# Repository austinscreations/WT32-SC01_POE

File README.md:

# WT32-SC01_POE

2023-06-28:

New sheild has been designed that is more universal. the deisgn is much smaller. uses a single 1.25mm jst conenctor to connect to the wt32-sc01 PLUS display.
adapter has been built for the WT32-S3-86s (replaces the 86v) 4" display. adapter in the works to support the orginal display as well

2022-06-23: renamed the repo as this project has evolved

There are now two shields designed for the wt32-sc01 display.
- one offers Ethernet + 802.1af POE
- second offers passive 12-24v POE + a 2.1mm jack

the thought with a passive board is that it's smaller allowing for more compact case designs to be built. and if you prefer to use 802.1af POE with the 2.1mm jack you can very eaily use a standard POE injector that normally cost about $6 from aliexpress to gain such functionality. with teh apssive baord however you are limited to using wifi.

both shields also equipped with qwiic connector for easy i2c support

designed for the use case of using the panel for homeautomation, code and gui in progress.

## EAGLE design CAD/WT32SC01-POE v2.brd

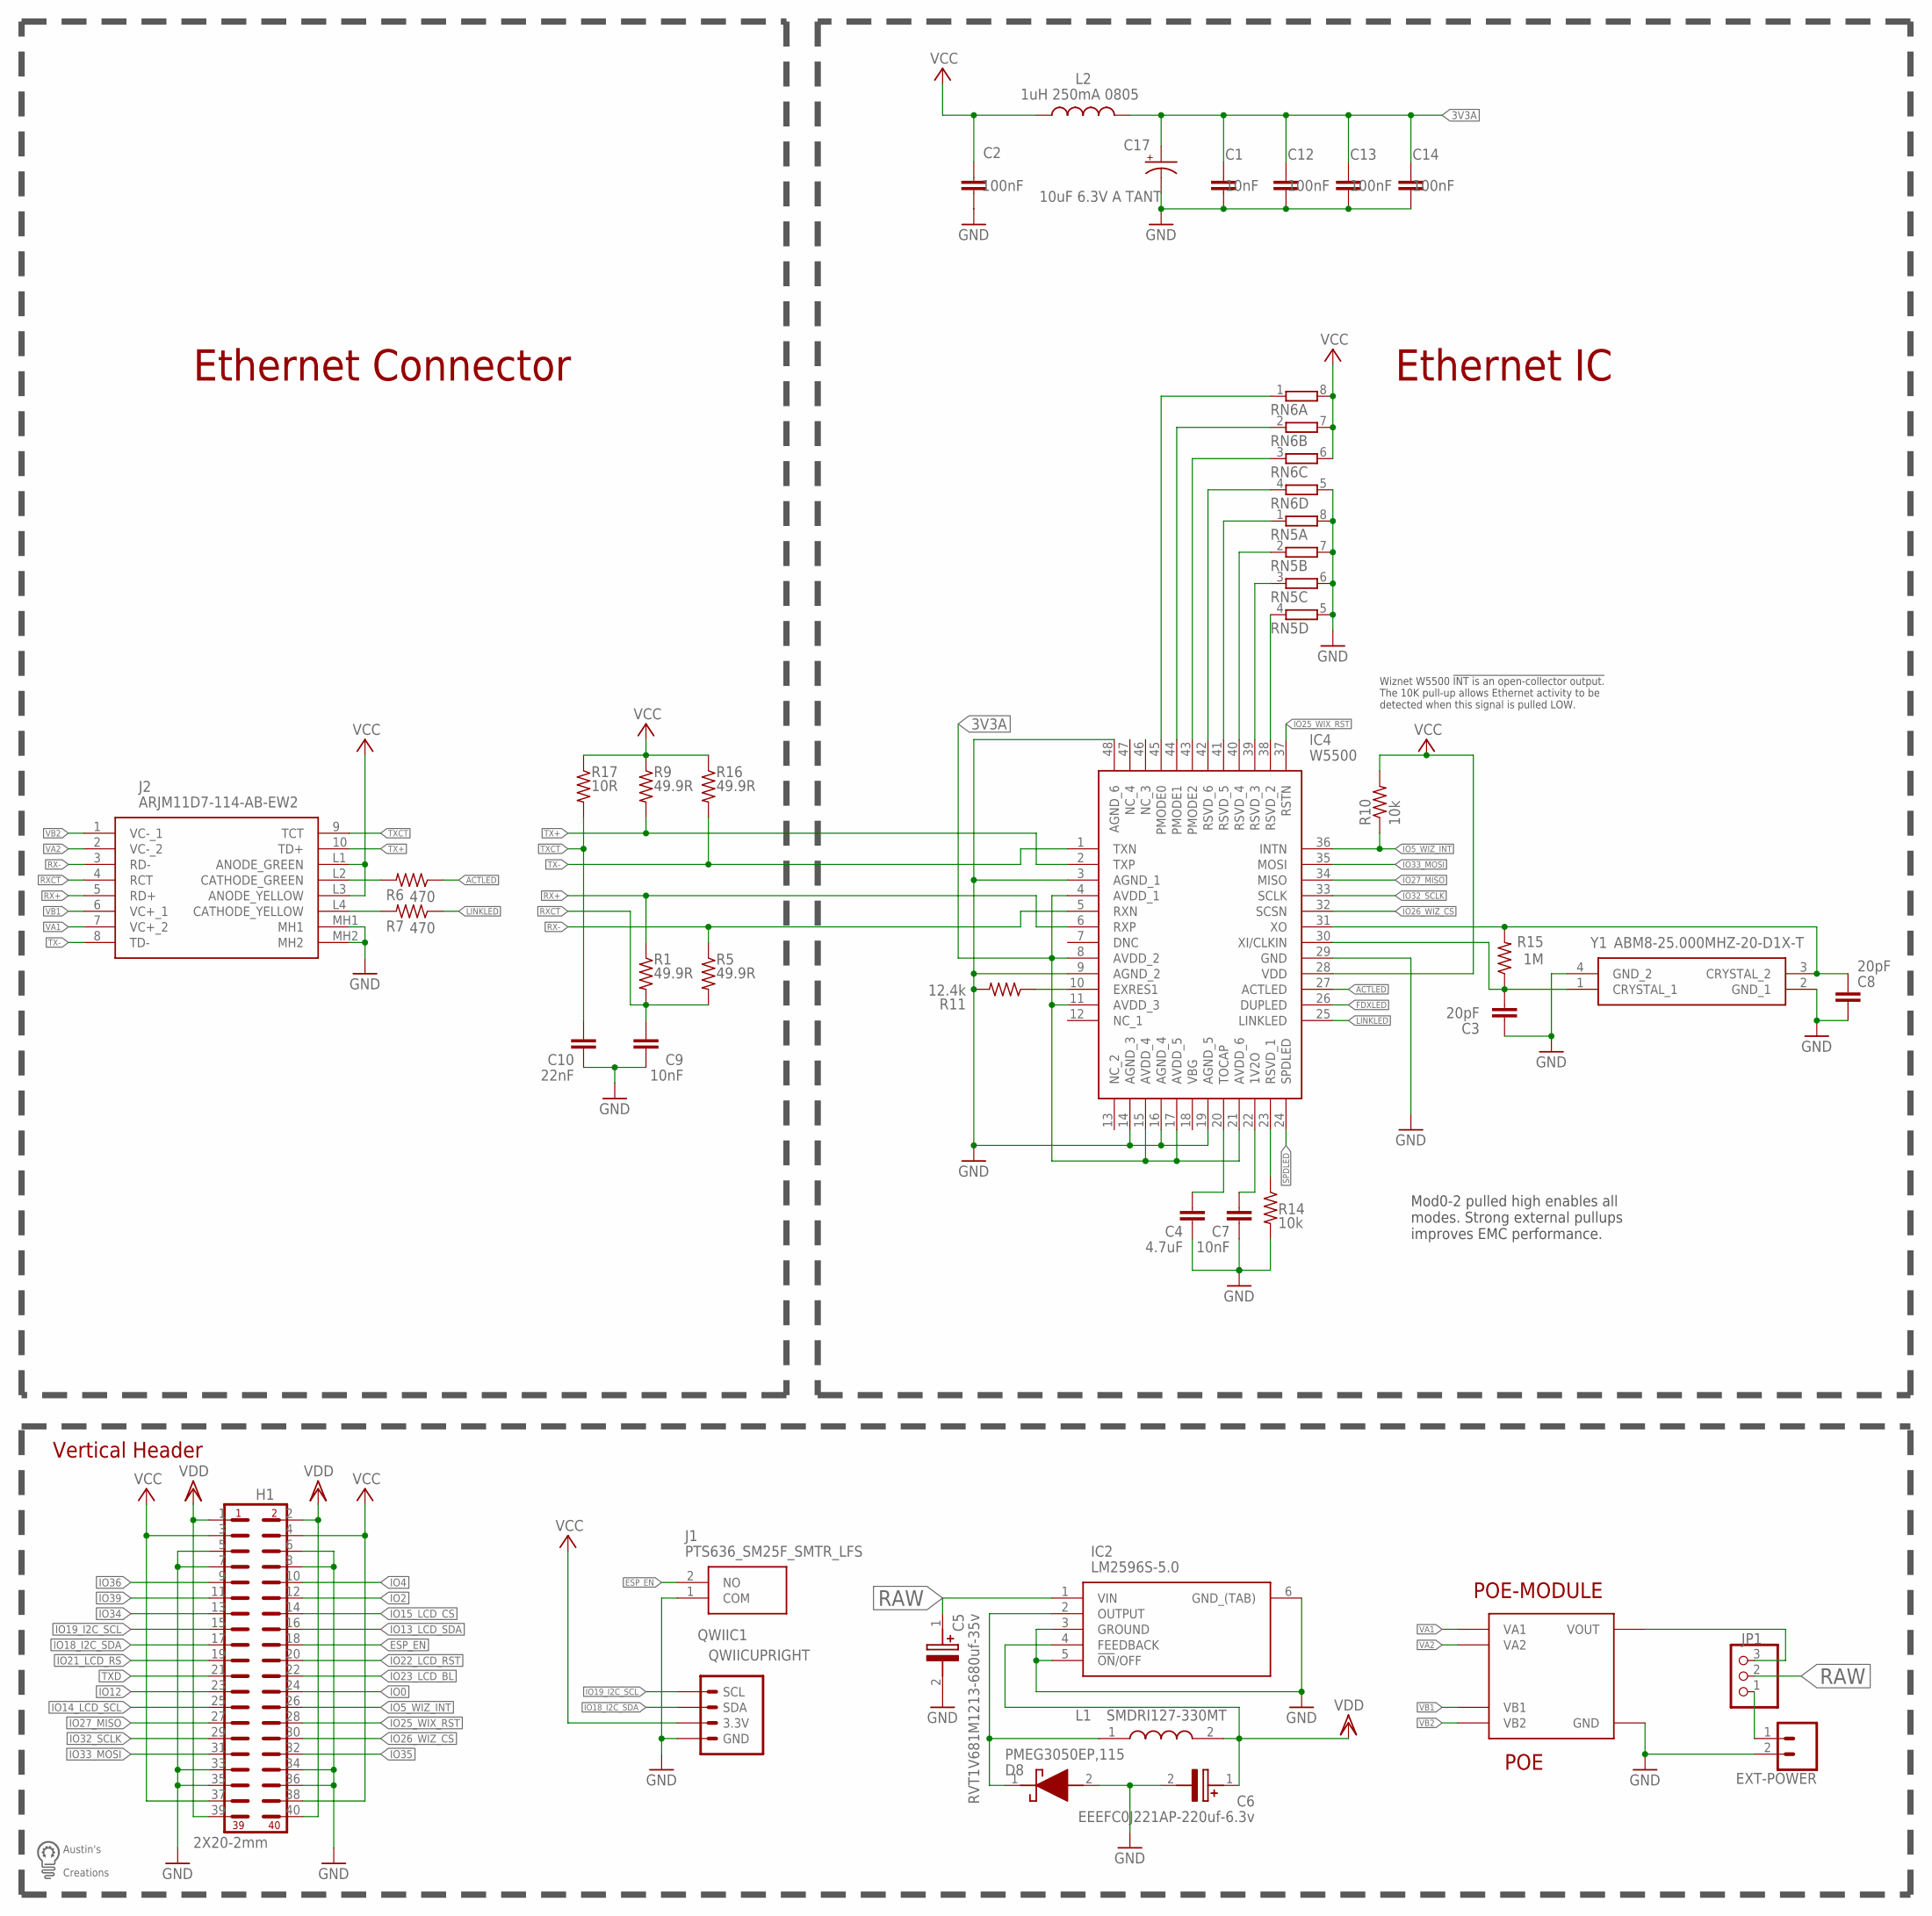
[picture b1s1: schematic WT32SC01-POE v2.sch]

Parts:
C1, C7, C9: 10nF; C0603
C2, C12, C13, C14: 100nF; C0603
C3, C8: 20pF; C0603
C4: 4.7uF; C0603
C5: RVT1V681M1213-680uf-35v; CAPAE1350X1400N
C6: EEEFC0J221AP-220uf-6.3v; CAPAE830X650N
C10: 22nF; C0603
C17: 10uF 6.3V A TANT; A/3216-18W
D8: PMEG3050EP,115; PMEG3050EP115
EXT-POWER: JL301-50002U02; SCREWTERMINAL-5MM-2
H1: 2X20-2mm; 2X20-2.00-P-BELOW
IC2: LM2596S-5.0; TO170P1435X465-6N
IC4: W5500; QFP50P900X900X160-48N
J1: PTS636_SM25F_SMTR_LFS; PTS636SM25FSMTRLFS
J2: ARJM11D7-114-AB-EW2; ARJM11D7114ABEW2
JP1: PINHD-1X3; 1X03
L1: SMDRI127-330MT; INDPM120120X800N
L2: 1uH 250mA 0805; L2012C
POE-MODULE: POE; DP1435
QWIIC1: QWIICUPRIGHT; BM04B-SRSS-TB
R1, R5, R9, R16: 49.9R; R0603
R6, R7: 470; R0603
R10, R14: 10k; R0603
R11: 12.4k; R0603
R15: 1M; R0603
R17: 10R; R0603
RN5, RN6: 4R-N0603-ARC; 0603-ARC
U$1: LOGOMED
Y1: ABM8-25.000MHZ-20-D1X-T; ABM825000MHZ10B1UT

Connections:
3V3A: C1.1, C12.1, C13.1, C14.1, C17.+, IC4.4 (AVDD_1), IC4.8 (AVDD_2), IC4.11 (AVDD_3), IC4.15 (AVDD_4), IC4.17 (AVDD_5), IC4.21 (AVDD_6), L2.2
ACTLED: IC4.27 (ACTLED), R6.1
ESP_EN: H1.18, J1.2 (NO)
FDXLED: IC4.26 (DUPLED)
GND: C1.2, C2.2, C3.1, C4.1, C5.2 (-), C6.2 (-), C7.1, C8.1, C9.1, C10.1, C12.2, C13.2, C14.2, C17.-, D8.2 (A), EXT-POWER.2, H1.5, H1.6, H1.7, H1.8, H1.33, H1.34, H1.35, H1.36, IC2.3 (GROUND), IC2.5 (!ON!/OFF), IC2.6 (GND_(TAB)), IC4.3 (AGND_1), IC4.9 (AGND_2), IC4.14 (AGND_3), IC4.16 (AGND_4), IC4.19 (AGND_5), IC4.29 (GND), IC4.48 (AGND_6), J1.1 (COM), J2.MH1, J2.MH2, POE-MODULE.GND, QWIIC1.1 (GND), R11.2, R14.2, RN5.5 (2), RN5.6 (2), RN5.7 (2), RN5.8 (2), RN6.5 (2), Y1.2 (GND_1), Y1.4 (GND_2)
IO0: H1.24
IO2: H1.12
IO4: H1.10
IO5_WIZ_INT: H1.26, IC4.36 (INTN), R10.1
IO12: H1.23
IO13_LCD_SDA: H1.16
IO14_LCD_SCL: H1.25
IO15_LCD_CS: H1.14
IO18_I2C_SDA: H1.17, QWIIC1.3 (SDA)
IO19_I2C_SCL: H1.15, QWIIC1.4 (SCL)
IO21_LCD_RS: H1.19
IO22_LCD_RST: H1.20
IO23_LCD_BL: H1.22
IO25_WIX_RST: H1.28, IC4.37 (RSTN)
IO26_WIZ_CS: H1.30, IC4.32 (SCSN)
IO27_MISO: H1.27, IC4.34 (MISO)
IO32_SCLK: H1.29, IC4.33 (SCLK)
IO33_MOSI: H1.31, IC4.35 (MOSI)
IO34: H1.13
IO35: H1.32
IO36: H1.9
IO39: H1.11
LINKLED: IC4.25 (LINKLED), R7.1
unnamed: EXT-POWER.1, JP1.1
unnamed: IC4.10 (EXRES1), R11.1
unnamed: IC4.23 (RSVD_1), R14.1
unnamed: IC4.38 (RSVD_2), RN5.4 (1)
unnamed: IC4.39 (RSVD_3), RN5.3 (1)
unnamed: IC4.40 (RSVD_4), RN5.2 (1)
unnamed: IC4.41 (RSVD_5), RN5.1
unnamed: IC4.42 (RSVD_6), RN6.4 (1)
unnamed: C8.2, IC4.31 (XO), R15.2, Y1.3 (CRYSTAL_2)
unnamed: IC4.43 (PMODE2), RN6.3 (1)
unnamed: IC4.44 (PMODE1), RN6.2 (1)
unnamed: IC4.45 (PMODE0), RN6.1
unnamed: C3.2, IC4.30 (XI/CLKIN), R15.1, Y1.1 (CRYSTAL_1)
unnamed: JP1.3, POE-MODULE.VOUT
unnamed: J2.L2 (CATHODE_GREEN), R6.2
unnamed: D8.1 (K), IC2.2 (OUTPUT), L1.1
unnamed: J2.L4 (CATHODE_YELLOW), R7.2
unnamed: C7.2, IC4.22 (1V2O)
unnamed: C4.2, IC4.20 (TOCAP)
RAW: C5.1 (+), IC2.1 (VIN), JP1.2
RX+: IC4.6 (RXP), J2.5 (RD+), R1.1
RX-: IC4.5 (RXN), J2.3 (RD-), R5.1
RXCT: C9.2, J2.4 (RCT), R1.2, R5.2
SPDLED: IC4.24 (SPDLED)
TX+: IC4.2 (TXP), J2.10 (TD+), R9.2
TX-: IC4.1 (TXN), J2.8 (TD-), R16.2
TXCT: C10.2, J2.9 (TCT), R17.2
TXD: H1.21
VA1: J2.7 (VC+_2), POE-MODULE.VA1
VA2: J2.2 (VC-_2), POE-MODULE.VA2
VB1: J2.6 (VC+_1), POE-MODULE.VB1
VB2: J2.1 (VC-_1), POE-MODULE.VB2
VCC: C2.1, H1.3, H1.4, H1.37, H1.38, IC4.28 (VDD), J2.L1 (ANODE_GREEN), J2.L3 (ANODE_YELLOW), L2.1, QWIIC1.2 (3.3V), R9.1, R10.2, R16.1, R17.1, RN6.6 (2), RN6.7 (2), RN6.8 (2)
VDD: C6.1 (+), H1.1, H1.2, H1.39, H1.40, IC2.4 (FEEDBACK), L1.2

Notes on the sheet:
Vertical Header
Mod0-2 pulled high enables all modes. Strong external pullups improves EMC performance.
Wiznet W5500 !INT is an open-collector output. The 10K pull-up allows Ethernet activity to be detected when this signal is pulled LOW.
Ethernet IC
Ethernet Connector

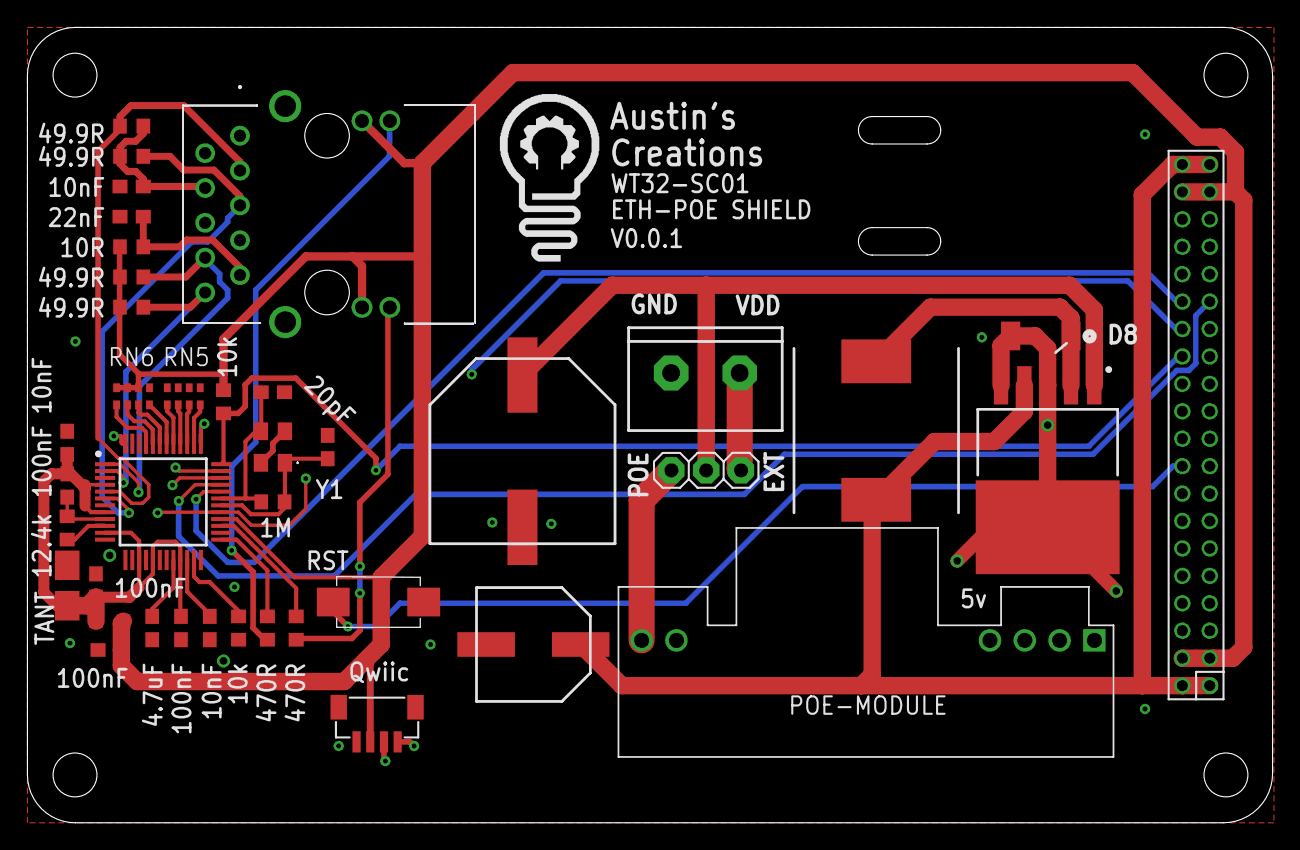
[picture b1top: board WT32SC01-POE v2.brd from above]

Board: 4 copper layers, 90.8 x 58.0 mm, 41 parts (0 on the bottom side), 45 nets.

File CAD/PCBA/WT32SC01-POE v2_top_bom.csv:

Comment,Designator,Footprint,LCSC Part #
1M,R15,R0603,C328343
1uH 250mA 0805,L2,L2012C,C98325
4.7uF,C4,C0603,C152930
10R,R17,R0603,C103222
10k,R10 R14,R0603,C103199
10nF,C1 C7 C9,C0603,C141077
10uF 6.3V A TANT,C17,A/3216-18W,C127946
12.4k,R11,R0603,C269455
20pF,C3 C8,C0603,C105621
22nF,C10,C0603,C302044
49.9R,R1 R5 R9 R16,R0603,C103679 
100nF,C2 C12 C13 C14,C0603,C83060
470R,R6 R7,R0603,C25241 
ABM8-25.000MHZ-20-D1X-T,Y1,ABM825000MHZ10B1UT,C258949
EEEFC0J221AP-220uf-6.3v,C6,CAPAE830X650N,C401613
LM2596S-5.0,IC2,TO170P1435X465-6N,C347421
PMEG4050EP 115,D8,PMEG4050EP115,C96235
PTS636_SM25F_SMTR_LFS,J1,PTS636SM25FSMTRLFS,C410373
QWIICUPRIGHT,QWIIC1,BM04B-SRSS-TB,C145961
RVT1V681M1213-680uf-35v,C5,CAPAE1350X1400N,C98216
SMDRI127-330MT,L1,INDPM120120X800N,C9400 
W5500,IC4,QFP50P900X900X160-48N,C32843
10k,RN5 RN6,R1206,C29718

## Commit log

2022-03-18 adding custom 3d printable wall plate mount
2022-03-18 example code
2022-03-26 accidental upload
2022-06-23 update for new boards
2022-06-23 preparing repo overhaul
2022-06-23 add new wifi and ethernet designs
2022-06-28 new versions
2022-06-28 obsolete design
2022-06-29 add case option for no usb
2022-06-29 add no usb case options
2023-06-28 adding latest POE shield
2023-08-02 adding 86s panel support
2023-08-02 add schematic image
2023-09-18 nudging the large inductor
2023-09-18 nudged the large inductor
2023-09-18 update inductor footprint
2024-05-23 rev 6 obsolete
    5v regulator not stable long term - new design coming
2024-05-23 add plus screen POE NA screen mount
2024-09-11 add the holder for the wt32sc01-plus screen
2024-09-11 Revert "add the holder for the wt32sc01-plus screen"
    This reverts commit c838f73afda2a925ba6b19c164f577740880c950.
